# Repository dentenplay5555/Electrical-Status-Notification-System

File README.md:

# Appliance Status Notifier (ระบบแจ้งเตือนสถานะอุปกรณ์ไฟฟ้า)

ระบบแจ้งเตือนสถานะอุปกรณ์ไฟฟ้าโดยตรวจจับกระแสไฟฟ้าแบบ near-realtime ด้วย ESP32 ร่วมกับ INA219 ส่งข้อมูลผ่าน Cloudflare Worker นำไปแสดงสถานะบนเว็บไซต์ และแจ้งเตือนสรุปประจำวันผ่าน LINE Messaging API ผ่าน LOA (Line Official Account) ทุกวันเวลา 16:10 น. โดยมีจุดประสงค์เป็นแนวทางการพัฒนาและต่อยอดเพิ่มขึ้นได้เรื่อยๆ ในด้านที่ท่านต้องการ<br>
----------
**รายละเอียดเพิ่มเติมสามารถดูได้ที่ folder ย่อยๆ หรือ documentation ข้างต้น**
**โครงงานการศึกษาค้นคว้าอิสระ (IS) <br>โรงเรียนนครสวรรค์ อำเภอเมืองนครสวรรค์ จังหวัดนครสวรรค์ ชั้นมัธยมศึกษาปีที่ 3**

---

## สารบัญ

- [ภาพรวมระบบ](#ภาพรวมระบบ)
- [สถาปัตยกรรม](#สถาปัตยกรรม)
- [คุณสมบัติ](#คุณสมบัติ)
- [โครงสร้างโปรเจกต์](#โครงสร้างโปรเจกต์)
- [ฮาร์ดแวร์ที่ใช้](#ฮาร์ดแวร์ที่ใช้)
- [เริ่มต้นใช้งาน](#เริ่มต้นใช้งาน)
  - [1. Firmware (ESP32)](#1-firmware-esp32)
  - [2. Backend (Cloudflare Worker)](#2-backend-cloudflare-worker)
  - [3. Frontend (เว็บแสดงสถานะ)](#3-frontend-เว็บแสดงสถานะ)
- [API Endpoints](#api-endpoints)
- [ผู้จัดทำ](#ผู้จัดทำ)
- [License](#license)

---

## ภาพรวมระบบและขอบเขต

ระบบนี้ตรวจจับสถานะเปิด/ปิดของ**อุปกรณ์ไฟฟ้ากระแสตรง (DC ช่วงแรงดัน 3–9 V)** เช่น พัดลมระบายความร้อน DC, เซอร์โวมอเตอร์ (Servo Motor) หรือชุดหลอดไฟส่องสว่าง โดยวัดกระแส แรงดัน และกำลังไฟฟ้าผ่านเซนเซอร์ INA219 ประมวลผลด้วย ESP32 DevKit แล้วส่งข้อมูลไปยัง Cloudflare Worker แบบ Near Real-time (รอบส่งข้อมูลทุก 10 วินาที) เพื่อนำไปแสดงผลบน Dashboard เว็บไซต์ พร้อมระบบสรุปการใช้พลังงานประจำวันผ่าน LINE Official Account (LOA) ทุกวันเวลา 16:10 น.

> **ขอบเขตการทำงาน (Scope & Limitations)**:
> - รองรับเฉพาะโหลดไฟฟ้ากระแสตรง (DC Load) แรงดัน 3.0 V – 9.0 V (ห้ามใช้กับไฟกระแสสลับ AC 220V เด็ดขาด)
> - รองรับกระแสไฟฟ้าสูงสุดไม่เกิน 3.2 A ตามสเปกชิป INA219 (Shunt Resistor 0.1 Ω)
> - ป้องกันสถานะกระพริบและการแจ้งเตือนผิดพลาดจากกระแส Standby ด้วยระบบ Hysteresis 2 ขอบ (ค่าเริ่มต้น: เปิด > 25 mA / ปิด < 15 mA ต้องปรับตามโหลดจริงที่วัดได้ ดูหัวข้อผลการทดลอง)

## สถาปัตยกรรมระบบ (Architecture)

```mermaid
flowchart LR
    A[ESP32 DevKit<br/>+ INA219 x2] -->|HTTP POST + Bearer Auth<br/>รอบละ 10s| B[Cloudflare Worker<br/>/update]
    B --> C[(Cloudflare D1<br/>latest_status + readings)]
    C --> D[Website Dashboard<br/>Polling ทุก 5s / N/A ถ้าเกิน 30s]
    C --> E[Cron Trigger<br/>09:10 UTC = 16:10 น.]
    E --> F[LINE Messaging API<br/>สรุปสถิติประจำวัน]
```

### การจัดสรรฐานข้อมูล D1
- **ตาราง `latest_status`**: เก็บสถานะล่าสุดแบบ 1 แถวต่ออุปกรณ์ (UPSERT) เพื่อให้หน้าเว็บดึงข้อมูลได้เร็ว ทันที และไม่มีปัญหาเรื่องความล่าช้าในการซิงค์ข้อมูล
- **ตาราง `readings`**: เก็บประวัติการวัดค่าแบบ Time-Series Log ย้อนหลัง 7 วัน สำหรับคำนวณสถิติและพลังงานสูงสุดในสรุปประจำวัน (มีระบบ Prune ข้อมูลเก่าอัตโนมัติ)

### รอบการส่งข้อมูลและความหน่วง (Cycle & Latency Analysis)
ระบบนี้ทำงานแบบ Near Real-Time ความหน่วงแต่ละช่วงด้านล่างเป็น **ค่าตามการออกแบบ (ยังไม่ได้วัดจริง)** จะอัปเดตเป็นค่าที่วัดได้เมื่อทดสอบเสร็จ (ดูหัวข้อผลการทดลอง):
1. **อ่านค่าจากเซนเซอร์ (I2C)**: สุ่มทุก 1 วินาที
2. **ประมวลผลบน ESP32**: ตรวจเกณฑ์ Hysteresis และสร้าง JSON
3. **ส่ง HTTP POST ผ่าน Wi-Fi ไป Cloudflare Worker**: ขึ้นกับสัญญาณ Wi-Fi และเครือข่าย
4. **Worker ตรวจ Bearer Token และบันทึกลง D1**
5. **หน้าเว็บ Polling ทุก 5 วินาที**; ถ้าไม่มีข้อมูลใหม่เกิน 30 วินาที แสดง `N/A`
- **ความหน่วงรวม (End-to-End)**: เมื่อสถานะเปลี่ยน ESP32 ส่งทันทีในรอบสุ่มถัดไป (≤ 1 วินาที) เว็บจึงเห็นการเปลี่ยนภายในรอบ Polling 5 วินาที ส่วน Heartbeat 10 วินาทีใช้ยืนยันว่าอุปกรณ์ยังออนไลน์ ตัวเลขจริงจะรายงานหลังจับเวลา และไม่อ้างค่า latency ต่ำที่ยังไม่มีผลวัดยืนยัน

## ภาพผังวงจร (Circuit & Hardware)

ผังการเชื่อมต่อวงจรระหว่าง ESP32 DevKit, Expansion Board, INA219 เซนเซอร์คู่ และโหลด DC:

*(ไฟล์ KiCad ต้นฉบับ: [`hardware/Circut.kicad_pro`](hardware/Circut.kicad_pro) ดูรายละเอียดที่ [`hardware/README.md`](hardware/README.md))*

## ฮาร์ดแวร์ที่ใช้ (Requirement)

| ชิ้นส่วน | รายละเอียด |
|---|---|
| ESP32 DevKit | ไมโครคอนโทรลเลอร์หลัก |
| INA219 | เซนเซอร์วัดกระแส/แรงดัน/กำลังไฟฟ้า (I2C) |
| Expansion Board | บอร์ดเชื่อมต่อเซนเซอร์ + LED + สวิตช์เลือกแรงดัน |

## วิธีการเริ่มต้นใช้งาน
**มีความจำเป็นที่จะต้องติดตั้ง PlatformIO CLI, Node.js และ LOA จึงมีสิทธิใช้ Line Messaging API ได้(ตรวจโควตาข้อความต่อเดือนของแผนที่ใช้ได้ใน LINE Official Account Manager)**
**ข้อควรระวังสำหรับผู้ใช้ Linux การ upload code ผ่าน USB อาจเจอ error "access denied" ได้ ควรอนุญาตผ่าน serial port ที่ท่านประสงค์ใช้**

### 1. Firmware (ESP32)

```bash
cd firmware
# คัดลอก template config แล้วใส่ค่าจริง (ไฟล์นี้ถูก ignore แล้ว — ไม่ขึ้น git)
cp main-src/config.example.h main-src/config.h
# แก้ไข main-src/config.h ด้วย editor ของท่าน

pio run -e main --target compiledb   # สร้าง compile_commands.json สำหรับ LSP
pio run -e main --target upload      # อัปโหลดโค้ดขึ้นบอร์ด (main env)
pio device monitor                   # ดู Serial Monitor (Log)
# สำหรับทดสอบ i2c_scanner:
pio run -e testing --target upload
```

ค่าที่ต้องแก้ใน `firmware/main-src/config.h`:

```cpp
#define WIFI_SSID     "WIFI NAME"
#define WIFI_PASSWORD "WIFI PASS"
#define API_ENDPOINT  "https://<your-worker>.workers.dev/update"
#define DEVICE_TOKEN  "your_secret_device_token"  // ต้องตรงกับ secret บน Worker
```

### 2. Backend (Cloudflare Worker)

```bash
cd backend
npm install
npx wrangler d1 create appliance-db     # สร้าง Database D1 ครั้งแรก
npx wrangler d1 execute appliance-db --remote --file=./schema.sql   # ต้องมี --remote ไม่งั้นสร้างตารางแค่ในเครื่อง
npx wrangler secret put LINE_ACCESS_TOKEN
npx wrangler secret put DEVICE_TOKEN    # ใส่ token เดียวกันกับใน config.h (ไม่งั้นจะตอบ 401)
npx wrangler deploy
```

### 3. Frontend (เว็บแสดงสถานะ)

Frontend เป็น static HTML/CSS/JS ใน `frontend/` — deploy อัตโนมัติผ่าน GitHub Actions ไปยัง **GitHub Pages** ทุกครั้งที่ push ไปยัง branch `master`

```bash
# แก้ API_URL ใน frontend/script.js ให้ตรงกับ Worker ของท่าน
# จากนั้น push ไปที่ branch master — workflow จะ deploy ให้อัตโนมัติ
git add frontend/
git commit -m "update frontend"
git push origin master
```

## API Endpoints 

| Method | Endpoint | คำอธิบาย |
|---|---|---|
| `POST` | `/update` | ESP32 ส่งค่าสถานะ/กระแส/กำลังไฟฟ้า (ต้องมี Bearer Token) |
| `GET` | `/status` | เว็บไซต์ดึงสถานะล่าสุดมาแสดงผล (ส่ง status: "N/A" ถ้าเกิน 30s) |
| `GET` | `/health` | ตรวจสอบว่า Worker ทำงานปกติ |
| `GET` | `/summary` | ดึงสถิติสรุปพลังงานประจำวัน |
| `GET` | `/history` | ดึงประวัติการวัดค่าย้อนหลัง |

## ผลการทดลองและการทดสอบระบบ (Experimental Results)

> **สถานะ: อยู่ระหว่างการวัดผล** ตารางด้านล่างเป็นแบบฟอร์มเปล่า กรอกเฉพาะค่าที่วัดได้จริงเท่านั้น และเก็บ log / รูปถ่าย / วิดีโอ ไว้เป็นหลักฐานใน `docs/evidence/` (ถ้ายังไม่ได้ทดสอบข้อใด ให้เว้นว่างไว้)
> เครื่องมือวัด: `ina-logger` (log กระแส/แรงดัน/กำลัง และสถิติ OFF/ON) และ Serial Monitor ของ firmware หลัก

### 1. การสอบเทียบเกณฑ์ ON/OFF และความแม่นยำของ INA219

วิธี: ต่อโหลดจริงผ่าน INA219, เก็บ I (mA) ช่วงปิด/เปิดอย่างน้อยช่วงละ 30 วินาที แล้วเทียบกับมัลติมิเตอร์

| โหลด | แรงดันแหล่งจ่าย (V) | I ตอน OFF สูงสุด (mA) | I ตอน ON ต่ำสุด (mA) | I มัลติมิเตอร์ (mA) | I INA219 เฉลี่ย (mA) | % ความคลาดเคลื่อน |
|---|---|---|---|---|---|---|
| | | | | | | |

เกณฑ์ที่เลือกใช้: `CURRENT_OFF_THRESHOLD_MA` = ____ , `CURRENT_ON_THRESHOLD_MA` = ____ (เหตุผล: ____)

### 2. การตรวจจับสถานะเปิด/ปิด (Detection)

| รายการทดสอบ | เงื่อนไข | จำนวนครั้ง | ถูกต้อง | ความแม่นยำ (%) | หมายเหตุ |
|---|---|:---:|:---:|:---:|---|
| ON | | | | | |
| OFF | | | | | |
| Standby / กระแสต่ำ | | | | | |
| ช่วงกลาง (Hysteresis) | | | | | |

### 3. ความหน่วงและการส่งข้อมูล

| รายการ | วิธีวัด | จำนวนครั้ง | min | เฉลี่ย | max |
|---|---|:---:|---|---|---|
| สลับโหลด → หน้าเว็บเปลี่ยนสถานะ (วินาที) | อัดวิดีโอจอคู่โหลด นับเฟรม | | | | |
| HTTP RTT ของ POST /update (ms) | พิมพ์เวลาใน Serial | | | | |
| ถอดไฟ ESP32 → หน้าเว็บขึ้น N/A (วินาที) | จับเวลา | | | | |
| ส่งสำเร็จ / ทั้งหมด ใน ____ ชั่วโมง | นับ `[api] HTTP 200` | | | | |

### 4. สภาวะขัดข้องและความปลอดภัย

| สภาวะ | การจำลอง | จำนวนครั้ง | ผลที่ได้ตามคาด | หมายเหตุ |
|---|---|:---:|:---:|---|
| ถอดสาย I2C ขณะทำงาน | ปลด SDA/SCL | | | ต้องส่ง `ok:false` |
| POST ไม่มี token / token ผิด | `curl` | | | ต้องได้ 401 |

### 5. สรุปประจำวันผ่าน LINE

| วันที่ | ตารางเปิด/ปิดโหลดที่จดไว้ | % ON ที่ควรได้ | % ON ที่ LINE ส่งมา | ได้รับข้อความเวลา |
|---|---|---|---|---|
| | | | | |

## คณะจัดทำ
- คณะผู้จัดทำ <br>
   1.ด.ช.กฤตภาส ใจใหญ่ เลขที่ 1 ม.3/1<br>
   2.ด.ช.กิตติศักดิ์ วงษา เลขที่ 4 ม.3/1<br>
   3.ด.ช.ปกรณ์เกียรติ แหวนแก้ว เลขที่ 15 ม.3/1<br>
   4.ด.ช.วรัญชัย พุทธวงค์ เลขที่ 19 ม.3/1<br>
   5.ด.ช.วิชญะ เสาไธสง เลขที่ 20 ม.3/1<br>
   6.ด.ช.อชิระ ลิ้มสุวรรณ เลขที่ 21 ม.3/1<br>
   
- ครูที่ปรึกษา <br>
   1.ครูศิรประภา ปิ่นเทศ<br>
   2.ครูสุพรรณี อภิชัยเอนก<br>
   3.ครูธันยาณัฐ รังสิยานนท์<br>
   
**โครงงานการศึกษาค้นคว้าอิสระ (Independent Study (IS)) ประจำปีการศึกษา 2569 <br>โรงเรียนนครสวรรค์ อำเภอเมืองนครสวรรค์ จังหวัดนครสวรรค์**

## License

โครงงานนี้เผยแพร่ภายใต้สัญญาอนุญาต [MIT License](LICENSE.txt)

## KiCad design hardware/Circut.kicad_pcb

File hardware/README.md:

# hardware/ — ไฟล์วงจร/PCB

ไฟล์ KiCad ของ expansion board ที่ออกแบบเอง สำหรับเชื่อมต่อ ESP32 DevKit กับเซนเซอร์ INA219 (ดูภาพรวมทั้งระบบที่ [README หลัก](../README.md))

## โครงสร้าง

```
hardware/
├── Circut.kicad_pro
├── Circut.kicad_sch
└── Circut.kicad_pcb
```

> **หมายเหตุ:** ชื่อไฟล์ `Circut` เป็นชื่อที่ตั้งไว้ตอนสร้างโปรเจกต์ (สะกดผิดจาก "Circuit") — ยังไม่ได้เปลี่ยนเพื่อหลีกเลี่ยง broken reference ใน KiCad

## รายละเอียดวงจร

Expansion board เชื่อมต่อกับ ESP32 DevKit ผ่าน pin header แบบถอดเปลี่ยนได้ ประกอบด้วย:

- จุดเชื่อมต่อเซนเซอร์ INA219 (I2C: SDA/SCL)
- ช่องจ่ายไฟเข้า 3 ทาง (DC Jack, USB Micro-B, USB Type-C) ผ่านไดโอดกันไฟย้อนกลับ (Diode-OR, 1N5819)
- สวิตช์เลือกแรงดันไฟฟ้าขาออก (3.3V หรือ 5V) สำหรับต่อขยายกับอุปกรณ์อื่น
- ไฟแสดงสถานะการทำงาน (Power LED)

## เปิดไฟล์

```bash
kicad hardware/Circut.kicad_pro
```

## ข้อควรระวังเฉพาะส่วนนี้

- **สำหรับผู้ที่ประสงค์ในการผลิต PCB** ก่อนสั่งผลิต PCB ตรวจสอบ footprint และ courtyard ให้ไม่ชนกันก่อนทุกครั้ง (DRC check)
- ไฟล์ backup ของ KiCad (`*-backups/`, `*.kicad_pcb-bak`) และโฟลเดอร์ `.history/` ถูกกันไว้ใน `.gitignore` แล้ว ไม่ต้องกังวลเรื่องไฟล์รกใน repo ได้เลย

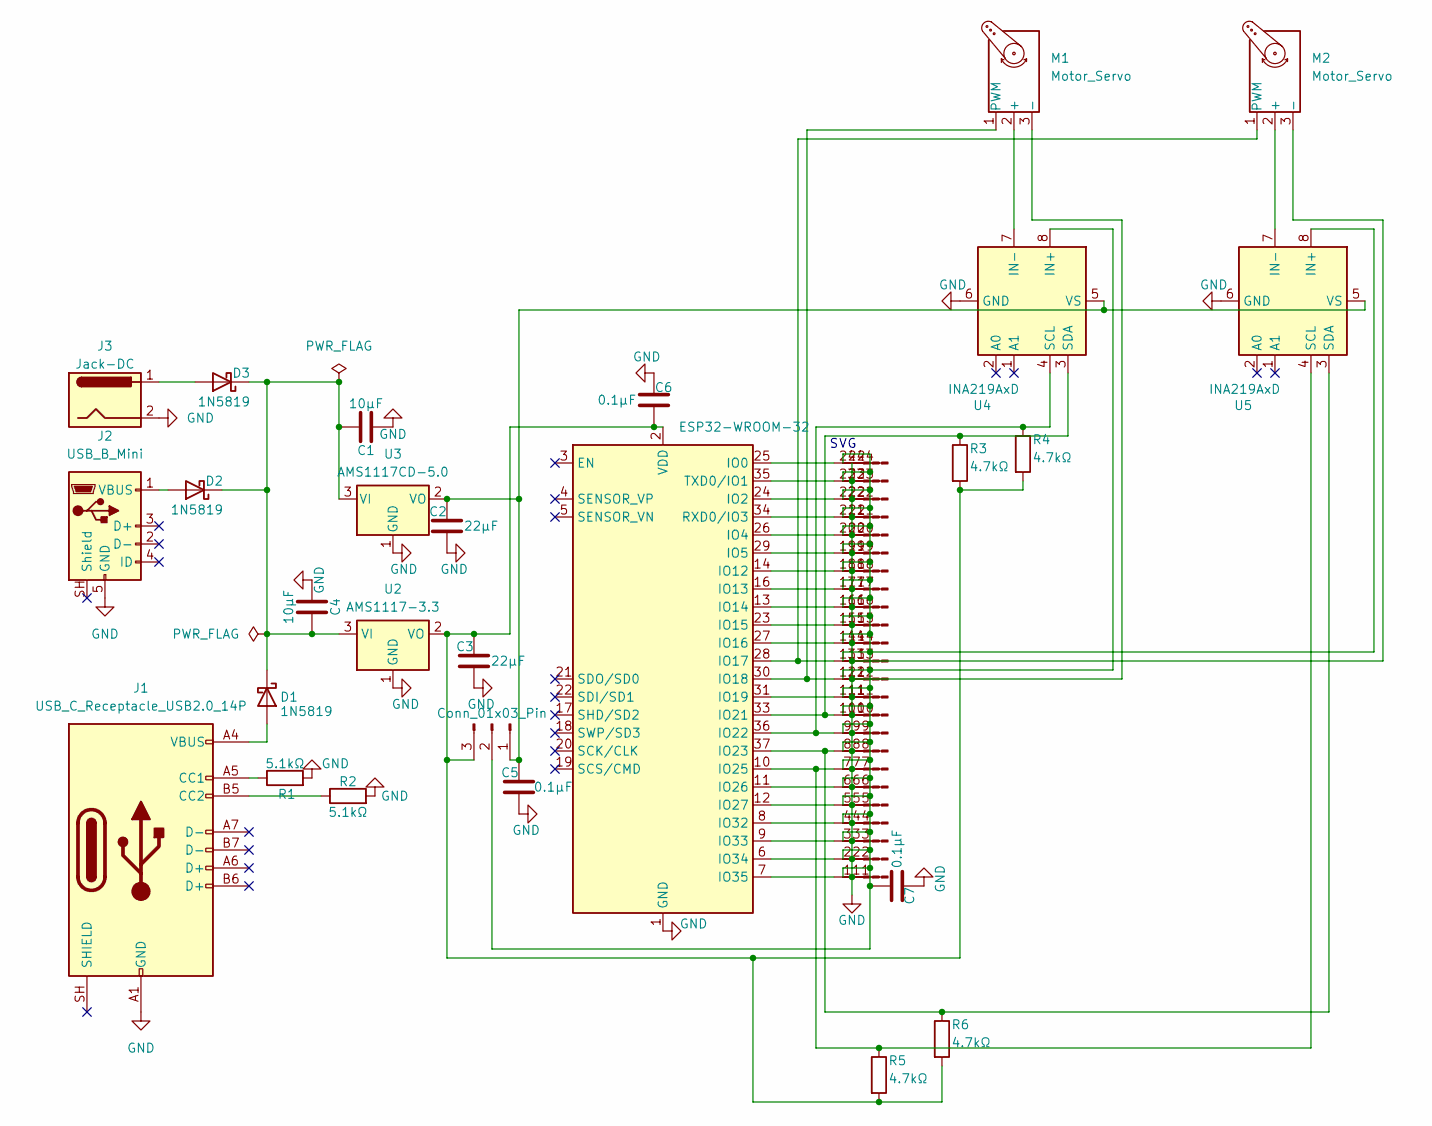
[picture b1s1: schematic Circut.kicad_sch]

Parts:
C1, C4: 10µF; C_0402_1005Metric_Pad0.74x0.62mm_HandSolder
C2, C3: 22µF; C_0402_1005Metric_Pad0.74x0.62mm_HandSolder
C5, C6, C7: 0.1µF; C_0402_1005Metric_Pad0.74x0.62mm_HandSolder
D1, D2, D3: 1N5819; D_0402_1005Metric
J1: USB_C_Receptacle_USB2.0_14P; USB_C_Receptacle_GCT_USB4085
J2: USB_B_Mini; USB_Mini-B_Lumberg_2486_01_Horizontal
J3: Jack-DC; BarrelJack_CUI_PJ-063AH_Horizontal
J4: Conn_01x24_Pin; PinHeader_1x24_P1.00mm_Vertical_SMD_Pin1Left
J5, J6: Conn_01x24_Pin; PinHeader_1x24_P1.00mm_Vertical_SMD_Pin1Right
J7: Conn_01x03_Pin; PinHeader_1x03_P1.00mm_Horizontal
M1, M2: Motor_Servo
R1, R2: 5.1kΩ; R_0402_1005Metric
R3, R4, R5, R6: 4.7kΩ; R_0402_1005Metric
U1: ESP32-WROOM-32
U2: AMS1117-3.3; SOT-223-3_TabPin2
U3: AMS1117CD-5.0; TO-252-3_TabPin2
U4, U5: INA219AxD; SOIC-8_3.9x4.9mm_P1.27mm

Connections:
GND: C1.2, C2.2, C3.2, C4.2, C5.2, C6.2, C7.2, J1.A1 (GND), J1.A12 (GND), J1.B1 (GND), J1.B12 (GND), J2.5 (GND), J3.2, J6.1, J6.2, J6.3, J6.4, J6.5, J6.6, J6.7, J6.8, J6.9, J6.10, J6.11, J6.12, J6.13, J6.14, J6.15, J6.16, J6.17, J6.18, J6.19, J6.20, J6.21, J6.22, J6.23, J6.24, M1.3 (-), M2.3 (-), R1.2, R2.2, U1.1 (GND), U1.15 (GND), U1.38 (GND), U1.39 (GND), U2.1 (GND), U3.1 (GND), U4.6 (GND), U5.6 (GND)
unnamed: D1.2 (A), J1.A4 (VBUS), J1.A9 (VBUS), J1.B4 (VBUS), J1.B9 (VBUS)
unnamed: C1.1, C4.1, D1.1 (K), D2.1 (K), D3.1 (K), U2.3 (VI), U3.3 (VI)
unnamed: D2.2 (A), J2.1 (VBUS)
unnamed: D3.2 (A), J3.1
unnamed: J1.A5 (CC1), R1.1
unnamed: J1.B5 (CC2), R2.1
unnamed: J4.1, U1.7 (IO35)
unnamed: J4.2, U1.6 (IO34)
unnamed: J4.3, U1.9 (IO33)
unnamed: J4.4, U1.8 (IO32)
unnamed: J4.5, U1.12 (IO27)
unnamed: J4.6, U1.11 (IO26)
unnamed: J4.7, R5.1, U1.10 (IO25), U5.4 (SCL)
unnamed: J4.8, R6.1, U1.37 (IO23), U5.3 (SDA)
unnamed: J4.9, R4.1, U1.36 (IO22), U4.4 (SCL)
unnamed: J4.10, R3.1, U1.33 (IO21), U4.3 (SDA)
unnamed: J4.11, U1.31 (IO19)
unnamed: J4.12, M1.1 (PWM), U1.30 (IO18)
unnamed: J4.13, M2.1 (PWM), U1.28 (IO17)
unnamed: J4.14, U1.27 (IO16)
unnamed: J4.15, U1.23 (IO15)
unnamed: J4.16, U1.13 (IO14)
unnamed: J4.17, U1.16 (IO13)
unnamed: J4.18, U1.14 (IO12)
unnamed: J4.19, U1.29 (IO5)
unnamed: J4.20, U1.26 (IO4)
unnamed: J4.21, U1.34 (RXD0/IO3)
unnamed: J4.22, U1.24 (IO2)
unnamed: J4.23, U1.35 (TXD0/IO1)
unnamed: J4.24, U1.25 (IO0)
unnamed: C7.1, J5.1, J5.2, J5.3, J5.4, J5.5, J5.6, J5.7, J5.8, J5.9, J5.10, J5.11, J5.12, J5.13, J5.14, J5.15, J5.16, J5.17, J5.18, J5.19, J5.20, J5.21, J5.22, J5.23, J5.24, J7.2, U4.8 (IN+), U5.8 (IN+)
unnamed: C2.1, C5.1, J7.1, U3.2 (VO), U4.5 (VS), U5.5 (VS)
unnamed: C3.1, C6.1, J7.3, R3.2, R4.2, R5.2, R6.2, U1.2 (VDD), U2.2 (VO)
unnamed: M1.2 (+), U4.7 (IN-)
unnamed: M2.2 (+), U5.7 (IN-)

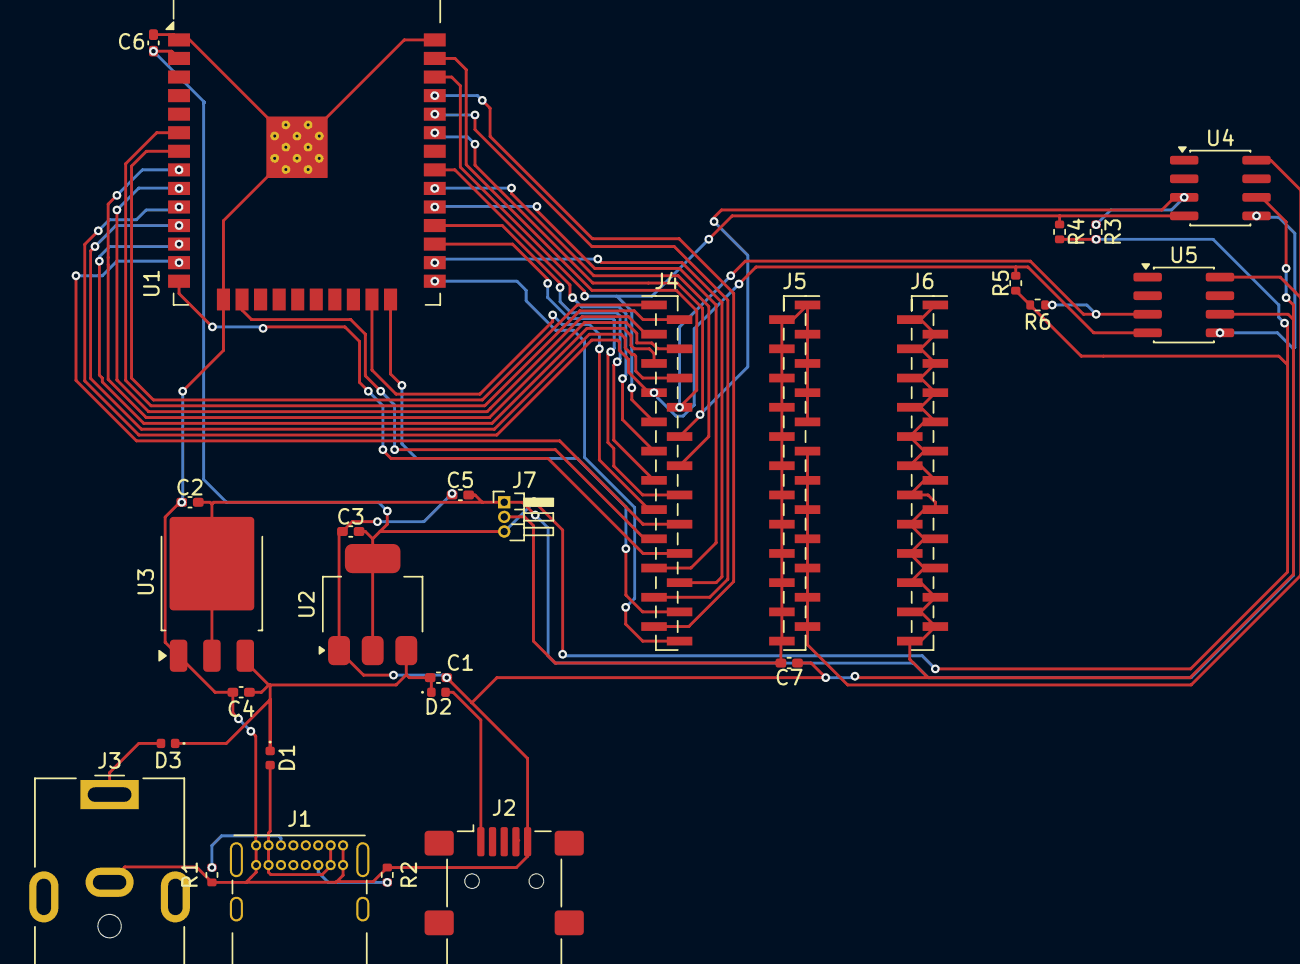
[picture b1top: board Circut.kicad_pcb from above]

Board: 2 copper layers, 28 parts (0 on the bottom side), 34 nets.

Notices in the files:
README.md:
License: MIT
